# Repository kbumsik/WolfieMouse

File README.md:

# WolfieMouse

WolfieMouse is a robotics project to build [a micromouse](https://en.wikipedia.org/wiki/Micromouse). This project covers three parts:

* Robotics algorithm for maze solving (C++)
* low-level hardware driver software (C and ARM assembly)
* Tools to capture and plot robot's sensor data (Python)
* Embedded hardware design and PCB design (KiCad, an open-source alternative to Altium)

This robot won:
  * **The Special Mention Award in 2018 IEEE Region 1 Micromouse Robotics Competition**.
  * **The 3rd Place Award in 2019 IEEE Region 1 Micromouse Robotics Competition**.

## Get started

If you don't know what is micromouse competition, [this document will help.](doc/What-is-Micromouse.md).

Requires tools:
* [GNU Arm Embedded Toolchain](https://developer.arm.com/open-source/gnu-toolchain/gnu-rm) and [Makefile](https://www.gnu.org/software/make/manual/make.html) to build program for the robot.
* [OpenOCD](http://openocd.org/) to upload the program to the robot and to debug.
* [KiCad](http://kicad.org/) to design a PCB hardware.

Otherwise, a [Vagrant](https://www.vagrantup.com/) virtual machine environment is provided to skip installing the above tools.

If you whish to start with this project, see [get stared document](doc/Get-started.md).

## Documentation

See [documentation section.](doc/)

## Directory descriptions

* `doc`: Documentation folder
* `firmware`: The robot's program folder, including robotics algorithms and hardware drivers
* `simulation`: Programs to test algorithms on a desktop computer
* `tools`: Contains robot sensor data capturing tools and scripts for Vagrant machine.

## Gallery

Terminal-based simulation program. `M` stands for the position of the robot, `D` stands for the position of the goal in the maze, and `S` stands for the starting position.

Schematic overview.

PCB Footprint overview.

## License and Credits

Source code in `firmware` and `simulation` folders are licensed under [GPLv2.1](https://www.gnu.org/licenses/old-licenses/lgpl-2.1.en.html).

External libraries (FreeRTOS, CMSIS, STM32F4 HAL) under `firmware/lib` follow their own terms.

The fundamental hardware design is inspired by [Project Futura](http://micromouseusa.com/?page_id=1342) by [Green Ye](http://www.greenye.net/).

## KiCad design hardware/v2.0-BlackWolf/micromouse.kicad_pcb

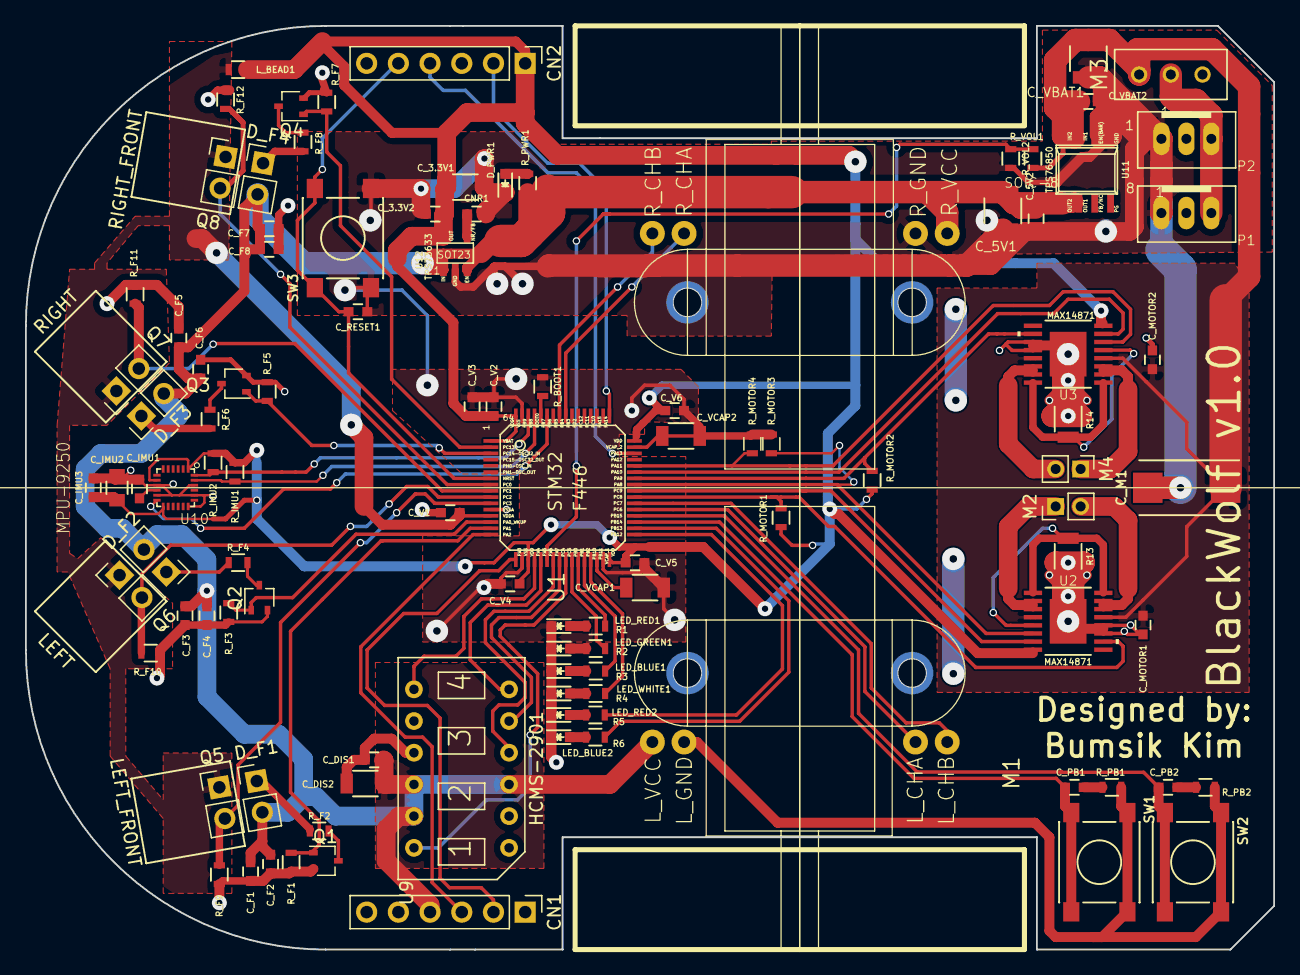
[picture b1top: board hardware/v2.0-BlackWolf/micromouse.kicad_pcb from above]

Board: 2 copper layers, 100.0 x 74.0 mm, 108 parts (0 on the bottom side), 73 nets.

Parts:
CN1, CN2: 6_PIN_HEADER; Pin_Header_Straight_1x06_Pitch2.54mm
CNR1: 0.1uF; C_0603
C_3.3V1: 10uF; C_1206
C_3.3V2, C_5V2: 0.1uF; C_0603
C_5V1: 100uF; C_1210
C_DIS1: 0.1uF; C_0603
C_DIS2: 10uF; C_1206
C_F1, C_F3, C_F5, C_F7: 4.7u; C_0603
C_F2, C_F4, C_F6, C_F8: 0.1u; C_0603
C_IMU1, C_IMU3: 0.1uF; C_0603
C_IMU2: 10nF; C_0805
C_M1: 220uF; TantalC_SizeD_EIA-7343_Reflow
C_MOTOR1, C_MOTOR2: 1uF; C_0603
C_PB1, C_PB2: 0.1uF; C_0603
C_RESET1: 0.1uF; C_0603
C_V1, C_V2, C_V3, C_V4, C_V5, C_V6: 0.1uF; C_0603
C_VBAT1: 100uF; C_1210
C_VBAT2: 0.1uF; C_0603
C_VCAP1: 4.7uF; C_1206
C_VCAP2: 2.2uF; C_1206
D_F1, D_F2, D_F3, D_F4: SFH 4545; Pin_Header_Straight_1x02_Pitch2.54mm
D_PWR1: Led_Small; LED_0603
LED_BLUE1, LED_BLUE2: Led_Small; LED_0603
LED_GREEN1: Led_Small; LED_0603
LED_RED1, LED_RED2: Led_Small; LED_0603
LED_WHITE1: Led_Small; LED_0603
LEFT: RANGE_SENSOR_HOUSING
LEFT_FRONT: RANGE_SENSOR_HOUSING
L_BEAD1: 10uH; R_0603
M1: MOTOR_MOUNTS_AND_ENCODERS; FUTURA-1.0-MOTOR-MOUNT-TEMPLATE
M2: LEFT_MOTOR; Pin_Header_Straight_1x02_Pitch2.00mm
M3: 2.54MM-SLIDE-SWITCH_TS02_SWITCH
M4: RIGHT_MOTOR; Pin_Header_Straight_1x02_Pitch2.00mm
P1, P2: B3B-PH-SM4-TB; JST_B3B-PH_HEADER
Q1, Q2, Q3, Q4: DMN3150LW; SOT-323_SC-70
Q5, Q6, Q7, Q8: TEFT4300; Pin_Header_Straight_1x02_Pitch2.54mm
R1, R2, R3, R4, R5, R6: 1k; R_0603
R13, R14: 62.5m; R_1206
RIGHT: RANGE_SENSOR_HOUSING
RIGHT_FRONT: RANGE_SENSOR_HOUSING
R_BOOT1: 10k; R_0603
R_F1, R_F3, R_F5, R_F7: 47k; R_0603
R_F2, R_F8: 10; R_0603
R_F4, R_F6: 20; R_0603
R_F9, R_F10, R_F11, R_F12: 2.4k; R_0603
R_IMU1, R_IMU2: 10k; R_0603
R_MOTOR1, R_MOTOR2, R_MOTOR3, R_MOTOR4: 10k; R_0603
R_PB1, R_PB2: 1k; R_0603
R_PWR1: 1k; R_0603
R_VOL1: 20k; R_0603
R_VOL2: 10k; R_0603
SW1, SW2, SW3: SWITCH_DPST; SW_SPST_PTS645
U1: STM32F446RE_LQFP64; STM32F446_LQFP64
U2, U3: MAX14871; TSSOP-16_EP
U9: HCMS-2901; HCMS-2903
U10: MPU-9250; QFN-24%2f3MM
U11: TPS76850; TPS76850_SOIC-8
U12: TPS73633; TPS73633_SOT-23

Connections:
+3.3VADC: C_V1.1, L_BEAD1.2, Q5.1, Q6.1, Q7.1, Q8.1, U1.VDDA
+3V3: CN2.1, C_3.3V1.1, C_3.3V2.1, C_IMU2.1, C_IMU3.1, C_V2.2, C_V3.1, C_V4.2, C_V5.2, C_V6.1, L_BEAD1.1, R_IMU1.1, R_IMU2.1, R_MOTOR1.1, R_MOTOR2.1, U1.VBAT, U1.VDD_, U2.8, U3.8, U10.1, U10.8, U10.13, U12.5
+5V: CN1.4, C_5V1.1, C_5V2.1, C_DIS1.1, C_DIS2.1, C_F1.1, C_F2.1, C_F3.1, C_F4.1, C_F5.1, C_F6.1, C_F7.1, C_F8.1, D_F1.2, D_F2.2, D_F3.2, D_F4.2, M1.L_VC, M1.R_VC, R_PWR1.1, U9.SEL, U9.V_LE, U9.V_LO, U11.5, U11.6, U12.1, U12.3
+BATT: C_M1.1, C_MOTOR1.1, C_MOTOR2.1, C_VBAT1.1, C_VBAT2.1, M3.PIN3, R_VOL1.1, U2.4, U2.13, U3.4, U3.13, U11.3, U11.4
BATT_LEVEL: R_VOL1.2, R_VOL2.1, U1.PA6
DIS_MOSI: U1.PA7, U9.D_IN
DIS_RS: U1.PC4, U9.RS
DIS_SCK: U1.PA5, U9.CLK
EMITTER_FL: Q1.1, R_F1.1, U1.PA1
EMITTER_FR: Q4.1, R_F7.1, U1.PC13
EMITTER_L: Q2.1, R_F3.1, U1.PA0_
EMITTER_R: Q3.1, R_F5.1, U1.PC14
GND: CN1.6, CN2.3, CNR1.2, C_3.3V1.2, C_3.3V2.2, C_5V1.2, C_5V2.2, C_DIS1.2, C_DIS2.2, C_F1.2, C_F2.2, C_F3.2, C_F4.2, C_F5.2, C_F6.2, C_F7.2, C_F8.2, C_IMU1.2, C_IMU2.2, C_IMU3.2, C_M1.2, C_MOTOR1.2, C_MOTOR2.2, C_RESET1.2, C_V1.2, C_V2.1, C_V3.2, C_V4.1, C_V5.1, C_V6.2, C_VBAT1.2, C_VBAT2.2, C_VCAP1.1, C_VCAP2.1, C_VCAP2.2, D_PWR1.1, LED_BLUE1.1, LED_BLUE2.1, LED_GREEN1.1, LED_RED1.1, LED_RED2.1, LED_WHITE1.1, M1.L_GN, M1.R_GN, P1.1, P2.1, Q1.2, Q2.2, Q3.2, Q4.2, R13.2, R14.2, R_BOOT1.1, R_F1.2, R_F3.2, R_F5.2, R_F7.2, R_F9.2, R_F10.2, R_F11.2, R_F12.2, R_MOTOR3.2, R_MOTOR4.2, R_PB1.2, R_PB2.2, R_VOL2.2, SW1.2, SW2.2, SW3.2, U1.VCAP, U1.VSSA, U1.VSS_, U2.11, U2.12, U2.EPAD, U3.11, U3.12, U3.EPAD, U9.BLAN, U9.GND, U10.9, U10.11, U10.18, U10.20, U10.22, U11.1, U11.2, U12.2
IMU_INT: U1.PB7, U10.12
IMU_SCL: R_IMU1.2, U1.PB8, U10.23
IMU_SDA: R_IMU2.2, U1.PB9, U10.24
LED1: R1.1, U1.PB1
LED2: R2.1, U1.PB0
LED3: R3.1, U1.PB2
LED4: R4.1, U1.PB10
LED5: R5.1, U1.PB12
LED6: R6.1, U1.PB13
MOTOR_L_DIR: U1.PC9, U2.7
MOTOR_L_PWM: R_MOTOR3.1, U1.PA8, U2.6
MOTOR_R_DIR: U1.PA10, U3.7
MOTOR_R_PWM: R_MOTOR4.1, U1.PA11, U3.6
unnamed: CNR1.1, U12.4
unnamed: C_IMU1.1, U10.10
unnamed: C_PB1.1, R_PB1.1
unnamed: C_PB2.1, R_PB2.1
unnamed: C_VCAP1.2, U1.PB11
unnamed: D_F1.1, R_F2.1
unnamed: D_F2.1, R_F4.1
unnamed: D_F3.1, R_F6.1
unnamed: D_F4.1, R_F8.1
unnamed: D_PWR1.2, R_PWR1.2
unnamed: LED_BLUE1.2, R3.2
unnamed: LED_BLUE2.2, R6.2
unnamed: LED_GREEN1.2, R2.2
unnamed: LED_RED1.2, R1.2
unnamed: LED_RED2.2, R5.2
unnamed: LED_WHITE1.2, R4.2
unnamed: M2.1, U2.2, U2.3
unnamed: M2.2, U2.14, U2.15
unnamed: M3.PIN2, P1.3, P2.3
unnamed: M4.1, U3.2, U3.3
unnamed: M4.2, U3.14, U3.15
unnamed: Q1.3, R_F2.2
unnamed: Q2.3, R_F4.2
unnamed: Q3.3, R_F6.2
unnamed: Q4.3, R_F8.2
unnamed: R13.1, U2.1, U2.5, U2.16
unnamed: R14.1, U3.1, U3.5, U3.16
unnamed: R_BOOT1.2, U1.BOOT
PB1: C_PB1.2, SW1.1, U1.PB14
PB2: C_PB2.2, SW2.1, U1.PB15
RECV_FL: Q5.2, R_F9.1, U1.PC3
RECV_FR: Q8.2, R_F12.1, U1.PC0
RECV_L: Q6.2, R_F10.1, U1.PC2
RECV_R: Q7.2, R_F11.1, U1.PC1
RESET: CN2.5, C_RESET1.1, SW3.1, U1.NRST
ROT_L_CHA: M1.L_CA, U1.PC6
ROT_L_CHB: M1.L_CB, U1.PC7
ROT_R_CHA: M1.R_CA, U1.PB4
ROT_R_CHB: M1.R_CB, U1.PB5
SWCLK: CN2.2, U1.PA14
SWDIO: CN2.4, U1.PA13
USART_RX: CN1.2, U1.PA3
USART_TX: CN1.3, U1.PA2
~DIS_CE: U1.PA4, U9.CE
~DIS_RESET: U1.PC5, U9.RESE
~MOTOR_L_FAULT: R_MOTOR1.2, U1.PC8, U2.10
~MOTOR_R_FAULT: R_MOTOR2.2, U1.PA9, U3.10

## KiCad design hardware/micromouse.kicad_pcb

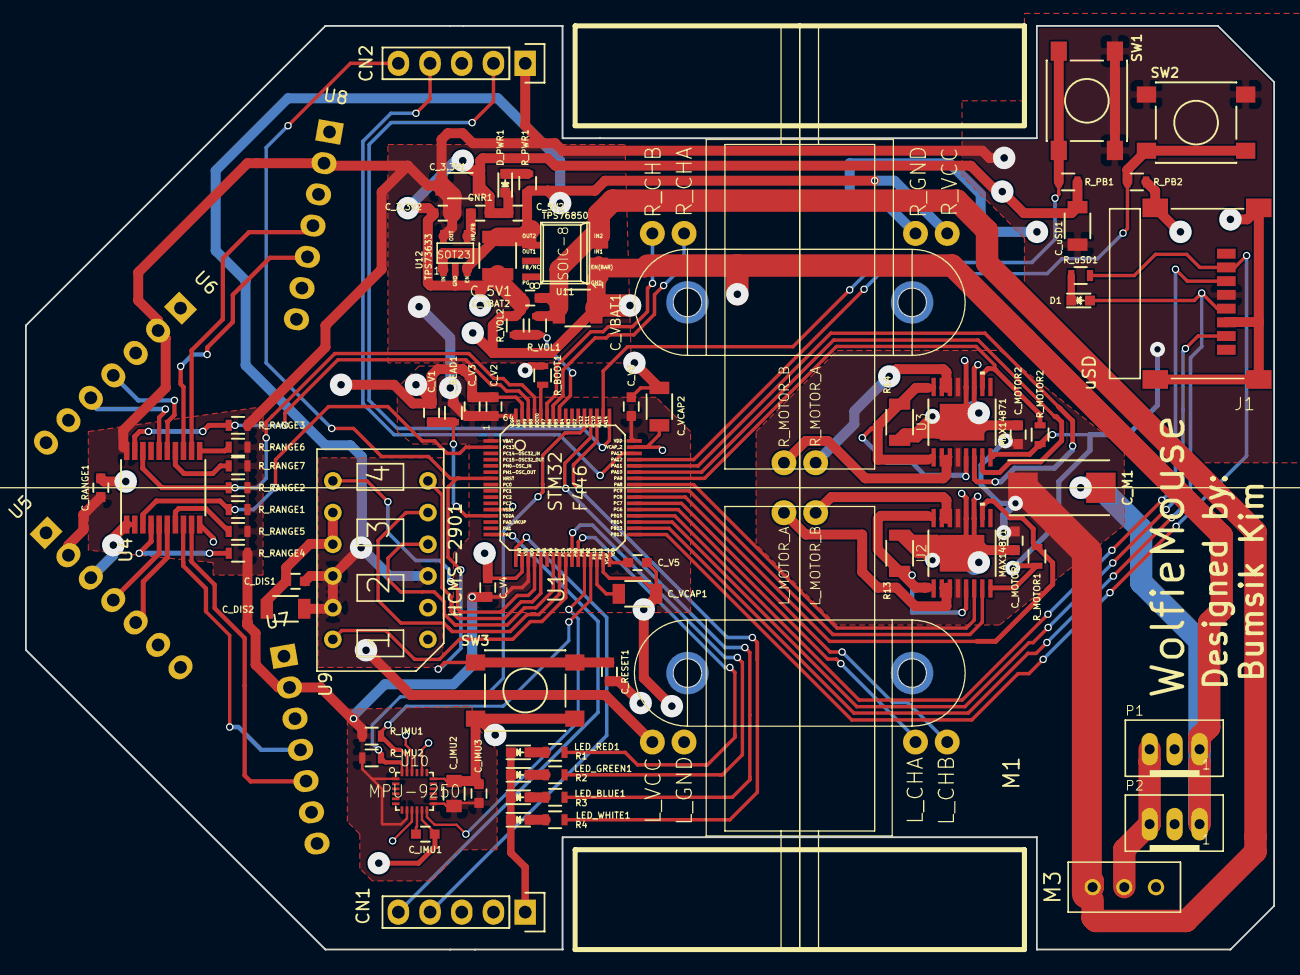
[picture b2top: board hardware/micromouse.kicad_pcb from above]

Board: 2 copper layers, 100.0 x 74.0 mm, 79 parts (0 on the bottom side), 71 nets.

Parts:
CN1, CN2: 5_PIN_HEADER; Pin_Header_Straight_1x05
CNR1: 0.1uF; C_0603
C_3.3V1: 10uF; C_1206
C_3.3V2, C_5V2: 0.1uF; C_0603
C_5V1: 100uF; C_1210
C_DIS1: 0.1uF; C_0603
C_DIS2: 10uF; C_1206
C_IMU1, C_IMU3: 0.1uF; C_0603
C_IMU2: 10nF; C_0805
C_M1: 220uF; TantalC_SizeD_EIA-7343_Reflow
C_MOTOR1, C_MOTOR2: 1uF; C_0603
C_RANGE1: 0.1uF; C_0603
C_RESET1: 0.1uF; C_0603
C_V1, C_V2, C_V3, C_V4, C_V5, C_V6: 0.1uF; C_0603
C_VBAT1: 100uF; C_1210
C_VBAT2: 0.1uF; C_0603
C_VCAP1, C_VCAP2: 2.2uF; C_1206
C_uSD1: 10uF; C_1206
D1: Led_Small; LED_0603
D_PWR1: Led_Small; LED_0603
J1: uSD_SLOT_47219-2001; uSD_MOLEX_47219-2001
LED_BLUE1: Led_Small; LED_0603
LED_GREEN1: Led_Small; LED_0603
LED_RED1: Led_Small; LED_0603
LED_WHITE1: Led_Small; LED_0603
L_BEAD1: 10uH; R_0603
M1: MOTOR_MOUNTS_AND_ENCODERS; FUTURA-1.0-MOTOR-MOUNT-TEMPLATE
M3: 2.54MM-SLIDE-SWITCH_TS02_SWITCH
P1, P2: B3B-PH-SM4-TB; JST_B3B-PH_HEADER
R1, R2, R3, R4: 1k; R_0603
R13, R14: 62.5m; R_1206
R_BOOT1: 10k; R_0603
R_IMU1, R_IMU2: 10k; R_0603
R_MOTOR1, R_MOTOR2: 10k; R_0603
R_PB1, R_PB2: 47k; R_0603
R_PWR1: 1k; R_0603
R_RANGE1, R_RANGE2, R_RANGE3, R_RANGE4, R_RANGE5, R_RANGE6, R_RANGE7: 10k; R_0603
R_VOL1: 20k; R_0603
R_VOL2: 10k; R_0603
R_uSD1: 1k; R_0603
SW1, SW2, SW3: SWITCH_DPST; SW_SPST_PTS645
U1: STM32F446RE_LQFP64; STM32F446_LQFP64
U2, U3: MAX14871; TSSOP-16_EP
U4: TCA9545A; TSSOP-20_4.4x6.5mm_Pitch0.65mm
U5, U6, U7, U8: VL6180X_POLOLU; VL6180X_POLOLU_Pin_Header_Straight_1x07
U9: HCMS-2901; HCMS-2903
U10: MPU-9250; QFN-24%2f3MM
U11: TPS76850; TPS76850_SOIC-8
U12: TPS73633; TPS73633_SOT-23

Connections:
+3.3VADC: C_V1.1, L_BEAD1.2, U1.VDDA
+3V3: CN2.1, C_3.3V1.1, C_3.3V2.1, C_IMU2.1, C_IMU3.1, C_RANGE1.1, C_V2.2, C_V3.1, C_V4.2, C_V5.2, C_V6.2, C_uSD1.1, J1.4, L_BEAD1.1, R_IMU1.1, R_IMU2.1, R_MOTOR1.1, R_MOTOR2.1, R_RANGE1.1, R_RANGE2.1, R_RANGE3.1, R_RANGE4.1, R_RANGE5.1, R_RANGE6.1, R_RANGE7.1, SW1.2, SW2.2, U1.VBAT, U1.VDD_, U2.8, U3.8, U4.20, U5.2, U6.2, U7.2, U8.2, U10.1, U10.8, U10.13, U12.5
+5V: C_5V1.1, C_5V2.1, C_DIS1.1, C_DIS2.1, M1.L_VC, M1.R_VC, R_PWR1.1, U9.SEL, U9.V_LE, U9.V_LO, U11.5, U11.6, U12.1, U12.3
+BATT: C_M1.1, C_MOTOR1.1, C_MOTOR2.1, C_VBAT1.1, C_VBAT2.1, M3.PIN3, R_VOL1.1, U2.4, U2.13, U3.4, U3.13, U11.3, U11.4
DIS_MOSI: U1.PA7, U9.D_IN
DIS_RS: U1.PC4, U9.RS
DIS_SCK: U1.PA5, U9.CLK
GND: CN1.1, CN2.3, CNR1.2, C_3.3V1.2, C_3.3V2.2, C_5V1.2, C_5V2.2, C_DIS1.2, C_DIS2.2, C_IMU1.2, C_IMU2.2, C_IMU3.2, C_M1.2, C_MOTOR1.2, C_MOTOR2.2, C_RANGE1.2, C_RESET1.2, C_V1.2, C_V2.1, C_V3.2, C_V4.1, C_V5.1, C_V6.1, C_VBAT1.2, C_VBAT2.2, C_VCAP1.2, C_VCAP2.1, C_VCAP2.2, C_uSD1.2, D_PWR1.1, J1.6, J1.G1, J1.G2, J1.G3, J1.G4, LED_BLUE1.1, LED_GREEN1.1, LED_RED1.1, LED_WHITE1.1, M1.L_GN, M1.R_GN, P1.1, P2.1, R13.2, R14.2, R_BOOT1.1, R_PB1.2, R_PB2.2, R_VOL2.2, SW3.2, U1.VCAP, U1.VSSA, U1.VSS_, U2.11, U2.12, U2.EPAD, U3.11, U3.12, U3.EPAD, U4.1, U4.2, U4.10, U5.3, U6.3, U7.3, U8.3, U9.BLAN, U9.GND, U10.9, U10.11, U10.18, U10.20, U10.22, U11.1, U11.2, U12.2
IMU_INT: U1.PB2, U10.12
IMU_SCL: R_IMU1.2, U1.PB10, U10.23
IMU_SDA: R_IMU2.2, U1.PC12, U10.24
LED1: R1.1, U1.PB1
LED2: R2.1, U1.PB0
LED3: R3.1, U1.PC11
LED4: R4.1, U1.PC10
MOTOR_L_DIR: U1.PC9, U2.7
MOTOR_L_PWM: U1.PA8, U2.6
MOTOR_R_DIR: U1.PA10, U3.7
MOTOR_R_PWM: U1.PA11, U3.6
unnamed: CNR1.1, U12.4
unnamed: C_IMU1.1, U10.10
unnamed: C_VCAP1.1, U1.PB11
unnamed: D1.1, R_uSD1.2
unnamed: D_PWR1.2, R_PWR1.2
unnamed: LED_BLUE1.2, R3.2
unnamed: LED_GREEN1.2, R2.2
unnamed: LED_RED1.2, R1.2
unnamed: LED_WHITE1.2, R4.2
unnamed: M1.L_MA, U2.2, U2.3
unnamed: M1.L_MB, U2.14, U2.15
unnamed: M1.R_MA, U3.2, U3.3
unnamed: M1.R_MB, U3.14, U3.15
unnamed: M3.PIN2, P1.3, P2.3
unnamed: R13.1, U2.1, U2.5, U2.16
unnamed: R14.1, U3.1, U3.5, U3.16
unnamed: R_BOOT1.2, U1.BOOT
unnamed: R_RANGE4.2, U4.4
unnamed: R_RANGE5.2, U4.7
unnamed: R_RANGE6.2, U4.11
unnamed: R_RANGE7.2, U4.14
unnamed: U4.5, U5.4
unnamed: U4.6, U5.5
unnamed: U4.8, U7.4
unnamed: U4.9, U7.5
unnamed: U4.12, U8.4
unnamed: U4.13, U8.5
unnamed: U4.15, U6.4
unnamed: U4.16, U6.5
PB1: R_PB1.1, SW1.1, U1.PA15
PB2: R_PB2.1, SW2.1, U1.PA12
RANGE_SCL: R_RANGE2.2, U1.PB8, U4.18
RANGE_SDA: R_RANGE3.2, U1.PB9, U4.19
RESET: CN2.5, C_RESET1.1, SW3.1, U1.NRST
ROT_L_CHA: M1.L_CA, U1.PC6
ROT_L_CHB: M1.L_CB, U1.PC7
ROT_R_CHA: M1.R_CA, U1.PB6
ROT_R_CHB: M1.R_CB, U1.PB7
SWCLK: CN2.2, U1.PA14
SWDIO: CN2.4, U1.PA13
USART_RX: CN1.4, U1.PA3
USART_TX: CN1.5, U1.PA2
VOL_METER: R_VOL1.2, R_VOL2.1, U1.PB5
uSD_MISO: J1.7, U1.PB14
uSD_MOSI: J1.3, U1.PB15
uSD_SCK: D1.2, J1.5, U1.PB13
~DIS_CE: U1.PA4, U9.CE
~DIS_RESET: U1.PC5, U9.RESE
~MOTOR_L_FAULT: R_MOTOR1.2, U1.PC8, U2.10
~MOTOR_R_FAULT: R_MOTOR2.2, U1.PA9, U3.10
~RANGE_RESET: R_RANGE1.2, U1.PC13, U4.3
~uSD_SS: J1.2, R_uSD1.1, U1.PB12

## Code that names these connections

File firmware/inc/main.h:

/**
  ******************************************************************************
  * @file           : main.h
  * @brief          : Header for main.c file.
  *                   This file contains the common defines of the application.
  ******************************************************************************
  * This notice applies to any and all portions of this file
  * that are not between comment pairs USER CODE BEGIN and
  * USER CODE END. Other portions of this file, whether 
  * inserted by the user or by software development tools
  * are owned by their respective copyright owners.
  *
  * Copyright (c) 2018 STMicroelectronics International N.V. 
  * All rights reserved.
  *
  * Redistribution and use in source and binary forms, with or without 
  * modification, are permitted, provided that the following conditions are met:
  *
  * 1. Redistribution of source code must retain the above copyright notice, 
  *    this list of conditions and the following disclaimer.
  * 2. Redistributions in binary form must reproduce the above copyright notice,
  *    this list of conditions and the following disclaimer in the documentation
  *    and/or other materials provided with the distribution.
  * 3. Neither the name of STMicroelectronics nor the names of other 
  *    contributors to this software may be used to endorse or promote products 
  *    derived from this software without specific written permission.
  * 4. This software, including modifications and/or derivative works of this 
  *    software, must execute solely and exclusively on microcontroller or
  *    microprocessor devices manufactured by or for STMicroelectronics.
  * 5. Redistribution and use of this software other than as permitted under 
  *    this license is void and will automatically terminate your rights under 
  *    this license. 
  *
  * THIS SOFTWARE IS PROVIDED BY STMICROELECTRONICS AND CONTRIBUTORS "AS IS" 
  * AND ANY EXPRESS, IMPLIED OR STATUTORY WARRANTIES, INCLUDING, BUT NOT 
  * LIMITED TO, THE IMPLIED WARRANTIES OF MERCHANTABILITY, FITNESS FOR A 
  * PARTICULAR PURPOSE AND NON-INFRINGEMENT OF THIRD PARTY INTELLECTUAL PROPERTY
  * RIGHTS ARE DISCLAIMED TO THE FULLEST EXTENT PERMITTED BY LAW. IN NO EVENT 
  * SHALL STMICROELECTRONICS OR CONTRIBUTORS BE LIABLE FOR ANY DIRECT, INDIRECT,
  * INCIDENTAL, SPECIAL, EXEMPLARY, OR CONSEQUENTIAL DAMAGES (INCLUDING, BUT NOT
  * LIMITED TO, PROCUREMENT OF SUBSTITUTE GOODS OR SERVICES; LOSS OF USE, DATA, 
  * OR PROFITS; OR BUSINESS INTERRUPTION) HOWEVER CAUSED AND ON ANY THEORY OF 
  * LIABILITY, WHETHER IN CONTRACT, STRICT LIABILITY, OR TORT (INCLUDING 
  * NEGLIGENCE OR OTHERWISE) ARISING IN ANY WAY OUT OF THE USE OF THIS SOFTWARE,
  * EVEN IF ADVISED OF THE POSSIBILITY OF SUCH DAMAGE.
  *
  ******************************************************************************
  */

/* Define to prevent recursive inclusion -------------------------------------*/
#ifndef __MAIN_H__
#define __MAIN_H__

/* Includes ------------------------------------------------------------------*/

/* USER CODE BEGIN Includes */

/* USER CODE END Includes */

/* Private define ------------------------------------------------------------*/

#define EMITTER_FR_Pin GPIO_PIN_13
#define EMITTER_FR_GPIO_Port GPIOC
#define EMITTER_R_Pin GPIO_PIN_14
#define EMITTER_R_GPIO_Port GPIOC
#define RECV_FR_Pin GPIO_PIN_0
#define RECV_FR_GPIO_Port GPIOC
#define RECV_R_Pin GPIO_PIN_1
#define RECV_R_GPIO_Port GPIOC
#define RECV_L_Pin GPIO_PIN_2
#define RECV_L_GPIO_Port GPIOC
#define RECV_FL_Pin GPIO_PIN_3
#define RECV_FL_GPIO_Port GPIOC
#define EMITTER_L_Pin GPIO_PIN_0
#define EMITTER_L_GPIO_Port GPIOA
#define EMITTER_FL_Pin GPIO_PIN_1
#define EMITTER_FL_GPIO_Port GPIOA
#define USART_TX_Pin GPIO_PIN_2
#define USART_TX_GPIO_Port GPIOA
#define USART_RX_Pin GPIO_PIN_3
#define USART_RX_GPIO_Port GPIOA
#define disPIN_CE_BAR_Pin GPIO_PIN_4
#define disPIN_CE_BAR_GPIO_Port GPIOA
#define disPIN_SCK_Pin GPIO_PIN_5
#define disPIN_SCK_GPIO_Port GPIOA
#define BATT_LEVEL_Pin GPIO_PIN_6
#define BATT_LEVEL_GPIO_Port GPIOA
#define disPIN_MOSI_Pin GPIO_PIN_7
#define disPIN_MOSI_GPIO_Port GPIOA
#define disPIN_RS_Pin GPIO_PIN_4
#define disPIN_RS_GPIO_Port GPIOC
#define disPIN_RESET_BAR_Pin GPIO_PIN_5
#define disPIN_RESET_BAR_GPIO_Port GPIOC
#define LED1_PIN_Pin GPIO_PIN_0
#define LED1_PIN_GPIO_Port GPIOB
#define LED2_PIN_Pin GPIO_PIN_1
#define LED2_PIN_GPIO_Port GPIOB
#define usdPIN_SS_BAR_Pin GPIO_PIN_12
#define usdPIN_SS_BAR_GPIO_Port GPIOB
#define usdPIN_SCK_Pin GPIO_PIN_13
#define usdPIN_SCK_GPIO_Port GPIOB
#define usdPIN_MISO_Pin GPIO_PIN_14
#define usdPIN_MISO_GPIO_Port GPIOB
#define usdPIN_MOSI_Pin GPIO_PIN_15
#define usdPIN_MOSI_GPIO_Port GPIOB
#define counterPIN_L_CHA_Pin GPIO_PIN_6
#define counterPIN_L_CHA_GPIO_Port GPIOC
#define counterPIN_L_CHB_Pin GPIO_PIN_7
#define counterPIN_L_CHB_GPIO_Port GPIOC
#define motorPIN_L_FAULT_BAR_Pin GPIO_PIN_8
#define motorPIN_L_FAULT_BAR_GPIO_Port GPIOC
#define motorPIN_L_DIR_Pin GPIO_PIN_9
#define motorPIN_L_DIR_GPIO_Port GPIOC
#define motorPIN_L_PWM_Pin GPIO_PIN_8
#define motorPIN_L_PWM_GPIO_Port GPIOA
#define motorPIN_R_FAULT_BAR_Pin GPIO_PIN_9
#define motorPIN_R_FAULT_BAR_GPIO_Port GPIOA
#define motorPIN_R_DIR_Pin GPIO_PIN_10
#define motorPIN_R_DIR_GPIO_Port GPIOA
#define motorPIN_R_PWM_Pin GPIO_PIN_11
#define motorPIN_R_PWM_GPIO_Port GPIOA
#define PB2_PIN_Pin GPIO_PIN_12
#define PB2_PIN_GPIO_Port GPIOA
#define TMS_Pin GPIO_PIN_13
#define TMS_GPIO_Port GPIOA
#define TCK_Pin GPIO_PIN_14
#define TCK_GPIO_Port GPIOA
#define PB1_PIN_Pin GPIO_PIN_15
#define PB1_PIN_GPIO_Port GPIOA
#define LED4_PIN_Pin GPIO_PIN_10
#define LED4_PIN_GPIO_Port GPIOC
#define LED3_PIN_Pin GPIO_PIN_11
#define LED3_PIN_GPIO_Port GPIOC
#define SWO_Pin GPIO_PIN_3
#define SWO_GPIO_Port GPIOB
#define counterPIN_R_CHA_Pin GPIO_PIN_4
#define counterPIN_R_CHA_GPIO_Port GPIOB
#define counterPIN_R_CHB_Pin GPIO_PIN_5
#define counterPIN_R_CHB_GPIO_Port GPIOB
#define imu_INT_Pin GPIO_PIN_7
#define imu_INT_GPIO_Port GPIOB
#define imuPIN_SCL_Pin GPIO_PIN_8
#define imuPIN_SCL_GPIO_Port GPIOB
#define imuPIN_SDA_Pin GPIO_PIN_9
#define imuPIN_SDA_GPIO_Port GPIOB

/* ########################## Assert Selection ############################## */
/**
  * @brief Uncomment the line below to expanse the "assert_param" macro in the 
  *        HAL drivers code
  */
 #define USE_FULL_ASSERT    1U 

/* USER CODE BEGIN Private defines */

/* USER CODE END Private defines */

#ifdef __cplusplus
 extern "C" {
#endif
void _Error_Handler(char *, int);

#define Error_Handler() _Error_Handler(__FILE__, __LINE__)
#ifdef __cplusplus
}
#endif

#endif /* __MAIN_H__ */

/************************ (C) COPYRIGHT STMicroelectronics *****END OF FILE****/

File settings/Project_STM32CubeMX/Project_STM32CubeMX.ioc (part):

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Mcu.Name=STM32F446R(C-E)Tx
Mcu.Package=LQFP64
Mcu.UserName=STM32F446RETx
PA10.GPIOParameters=GPIO_Label
PA10.GPIO_Label=motorPIN_R_DIR
PA10.Signal=GPIO_Output
PA11.GPIOParameters=GPIO_Label
PA11.GPIO_Label=motorPIN_R_PWM
PA11.Signal=S_TIM1_CH4
PA12.GPIOParameters=GPIO_Label
PA12.GPIO_Label=PB2_PIN
PA12.Signal=GPXTI12
PA13.GPIOParameters=GPIO_Label
PA13.GPIO_Label=TMS
PA13.Mode=Trace-Asynchronous_SW
PA13.Signal=SYS_JTMS-SWDIO
PA14.GPIOParameters=GPIO_Label
PA14.GPIO_Label=TCK
PA14.Mode=Trace-Asynchronous_SW
PA14.Signal=SYS_JTCK-SWCLK
PA15.GPIOParameters=GPIO_Label
PA15.GPIO_Label=PB1_PIN
PA15.Signal=GPXTI15
PA2.GPIOParameters=GPIO_Label
PA2.GPIO_Label=USART_TX
PA2.Mode=Asynchronous
PA2.Signal=USART2_TX
PA3.GPIOParameters=GPIO_Label
PA3.GPIO_Label=USART_RX
PA3.Mode=Asynchronous
PA3.Signal=USART2_RX
PA4.GPIOParameters=GPIO_Label
PA4.GPIO_Label=disPIN_CE_BAR
PA4.Signal=GPIO_Output
PA5.GPIOParameters=GPIO_Label
PA5.GPIO_Label=disPIN_SCK
PA5.Mode=Full_Duplex_Master
PA5.Signal=SPI1_SCK
PA6.GPIOParameters=GPIO_Label
PA6.GPIO_Label=disPIN_MISO
PA6.Mode=Full_Duplex_Master
PA6.Signal=SPI1_MISO
PA7.GPIOParameters=GPIO_Label
PA7.GPIO_Label=disPIN_MOSI
PA7.Mode=Full_Duplex_Master
PA7.Signal=SPI1_MOSI
PA8.GPIOParameters=GPIO_Label
PA8.GPIO_Label=motorPIN_L_PWM
PA8.Signal=S_TIM1_CH1
PA9.GPIOParameters=GPIO_Label
PA9.GPIO_Label=motorPIN_R_FAULT_BAR
PA9.Signal=S_TIM1_CH2
PB0.GPIOParameters=GPIO_Label
PB0.GPIO_Label=LED1_PIN
PB0.Signal=GPIO_Output
PB1.GPIOParameters=GPIO_Label
PB1.GPIO_Label=LED2_PIN
PB1.Signal=GPIO_Output
PB10.GPIOParameters=GPIO_Label
PB10.GPIO_Label=imuPIN_SCL
PB10.Mode=I2C
PB10.Signal=I2C2_SCL
PB12.GPIOParameters=GPIO_Label
PB12.GPIO_Label=usdPIN_SS_BAR
PB12.Signal=SPI2_NSS
PB13.GPIOParameters=GPIO_Label
PB13.GPIO_Label=usdPIN_SCK
PB13.Mode=Full_Duplex_Master
PB13.Signal=SPI2_SCK
PB14.GPIOParameters=GPIO_Label
PB14.GPIO_Label=usdPIN_MISO
PB14.Mode=Full_Duplex_Master
PB14.Signal=SPI2_MISO
PB15.GPIOParameters=GPIO_Label
PB15.GPIO_Label=usdPIN_MOSI
PB15.Mode=Full_Duplex_Master
PB15.Signal=SPI2_MOSI
PB2.GPIOParameters=GPIO_Label
PB2.GPIO_Label=imuPIN_INT
PB2.Signal=GPXTI2
PB3.GPIOParameters=GPIO_Label
PB3.GPIO_Label=SWO
PB3.Mode=Trace-Asynchronous_SW
PB3.Signal=SYS_JTDO-SWO
PB5.GPIOParameters=GPIO_Label
PB5.GPIO_Label=VOL_METER_PIN
PB5.Signal=GPIO_Analog
PB6.GPIOParameters=GPIO_Label
PB6.GPIO_Label=rotPIN_L_CHA
PB6.Signal=S_TIM4_CH1
PB7.GPIOParameters=GPIO_Label
PB7.GPIO_Label=rotPIN_L_CHB
PB7.Signal=S_TIM4_CH2
PB8.GPIOParameters=GPIO_Label
PB8.GPIO_Label=rangePIN_SCL
PB8.Mode=I2C
PB8.Signal=I2C1_SCL
PB9.GPIOParameters=GPIO_Label
PB9.GPIO_Label=rangePIN_SDA
PB9.Mode=I2C
PB9.Signal=I2C1_SDA
PC10.GPIOParameters=GPIO_Label
PC10.GPIO_Label=LED4_PIN
PC10.Signal=GPIO_Output
PC11.GPIOParameters=GPIO_Label
PC11.GPIO_Label=LED3_PIN
PC11.Signal=GPIO_Output
PC12.GPIOParameters=GPIO_Label
PC12.GPIO_Label=imuPIN_SDA
PC12.Mode=I2C
PC12.Signal=I2C2_SDA
PC13.GPIOParameters=GPIO_Label,GPIO_ModeDefaultEXTI
PC13.GPIO_Label=rangePIN_RESET_BAR
PC13.GPIO_ModeDefaultEXTI=GPIO_MODE_EVT_RISING
PC13.Signal=GPXTI13
PC14-OSC32_IN.Signal=RCC_OSC32_IN
PC15-OSC32_OUT.Signal=RCC_OSC32_OUT
PC4.GPIOParameters=GPIO_Label
PC4.GPIO_Label=disPIN_RS
PC4.Signal=GPIO_Output
PC5.GPIOParameters=GPIO_Label
PC5.GPIO_Label=disPIN_RESET_BAR
PC5.Signal=GPIO_Output
PC6.GPIOParameters=GPIO_Label
PC6.GPIO_Label=rotPIN_R_CHA
PC6.Signal=S_TIM3_CH1
PC7.GPIOParameters=GPIO_Label
PC7.GPIO_Label=rotPIN_R_CHB
PC7.Signal=S_TIM3_CH2
PC8.GPIOParameters=GPIO_Label
PC8.GPIO_Label=motorPIN_L_FAULT_BAR
PC8.Signal=GPXTI8
PC9.GPIOParameters=GPIO_Label
PC9.GPIO_Label=motorPIN_L_DIR
PC9.Signal=GPIO_Output
PH0-OSC_IN.Signal=RCC_OSC_IN
PH1-OSC_OUT.Signal=RCC_OSC_OUT
RCC.HSE_VALUE=8000000
RCC.SYSCLKFreq_VALUE=90000000
RCC.SYSCLKSource=RCC_SYSCLKSOURCE_PLLCLK
board=NUCLEO-F446RE
boardIOC=true

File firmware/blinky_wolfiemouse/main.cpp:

#include "trace.h"
#include "tick.h"
// KB library
#include "system_config.h"
#include "gpio.h"
#include "terminal.h"
#include "hcms_290x_display.h"

// FreeRTOS
#include "FreeRTOS.h"
#include "portable.h" // TODO: Delete
#include "task.h"
#include "timers.h"
#include "queue.h"
#include "semphr.h"
#include "event_groups.h"

void on_pressed(void);

static void task_blinky(void *pvParameters);

/* Task Handlers */
TaskHandle_t task_blinky_handler;


int main(void)
{
    // initialize clock and system configuration
    system_init();

    // Initialize all configured peripherals
    peripheral_init();

    /* Initial LED Display message */
    hcms_290x_matrix("BOOT");

    // Set interrupt button
    gpio_init_t GPIO_InitStruct;
    GPIO_InitStruct.Mode = GPIO_MODE_INPUT;
    GPIO_InitStruct.Pull = NOPULL;
    gpio_isr_enable(B1_PORT, B1_PIN, &GPIO_InitStruct, RISING_EDGE);
    gpio_isr_register(B1_PORT, B1_PIN, on_pressed);


    // Toggle LED once
    gpio_toggle(LED1_PORT, LED1_PIN);
    gpio_toggle(LED2_PORT, LED2_PIN);
    gpio_toggle(LED3_PORT, LED3_PIN);
    gpio_toggle(LED4_PORT, LED4_PIN);
    gpio_toggle(LED5_PORT, LED5_PIN);
    gpio_toggle(LED6_PORT, LED6_PIN);

    // wait for .5 second
    delay_ms(500);
    gpio_toggle(LED1_PORT, LED1_PIN);
    gpio_toggle(LED2_PORT, LED2_PIN);
    gpio_toggle(LED3_PORT, LED3_PIN);
    gpio_toggle(LED4_PORT, LED4_PIN);
    gpio_toggle(LED5_PORT, LED5_PIN);
    gpio_toggle(LED6_PORT, LED6_PIN);

    trace_puts("Hello ARM World!");
    terminal_puts("Hello World!\n");

    BaseType_t result;
    /* definition and creation of defaultTask */
    result = xTaskCreate(
            task_blinky,            /* Pointer to the function that implements the task */
            "Blinky",               /* Text name for the task. This is to facilitate debugging only. It is not used in the scheduler */
            configMINIMAL_STACK_SIZE, /* Stack depth in words */
            NULL,                   /* Pointer to a task parameters */
            1,                      /* The task priority */
            &task_blinky_handler);  /* Pointer of its task handler, if you don't want to use, you can leave it NULL */

    if (result != pdPASS) {
        KB_DEBUG_ERROR("Creating task failed!!");
    }
    /* Do not put delay function in this section!
     * Because xTaskCreate will stop systick until the scheduler called */
    // TODO: check if it is true
    /* Start scheduler */
    vTaskStartScheduler();
    while (1) {
    }
}

void on_pressed(void)
{
    trace_puts("Button Pressed\n");
    return;
}

/* vBlinkyTask function */
void task_blinky(void *pvParameters)
{
    portTickType xLastWakeTime;
    /* Initialize xLastWakeTime for vTaskDelayUntil */
    /* This variable is updated every vTaskDelayUntil is called */
    xLastWakeTime = xTaskGetTickCount();

    uint32_t seconds = 0;

    while (1) {
        gpio_toggle(LED1_PORT, LED1_PIN);
        gpio_toggle(LED2_PORT, LED2_PIN);
        gpio_toggle(LED3_PORT, LED3_PIN);
        gpio_toggle(LED4_PORT, LED4_PIN);
        gpio_toggle(LED5_PORT, LED5_PIN);
        gpio_toggle(LED6_PORT, LED6_PIN);
        ++seconds;
        // Count seconds on the trace device.
        trace_printf("Second %u\n", seconds);

        /* Call this Task explicitly every 50ms ,NOT Delay for 50ms */
        vTaskDelayUntil(&xLastWakeTime, (500 / portTICK_RATE_MS));
    }

    /* It never goes here, but the task should be deleted when it reached here */
    vTaskDelete(NULL);
}

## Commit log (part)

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2016-01-18 updated basic CubeMX project
2016-01-19 updated working test project
2016-02-02 Added simulation and algorithm part - 80% completed.
2016-02-08 updated MouseController.cpp
2016-02-09 reverted the changes back
    --eric
2016-02-29 added example_main.cpp
2016-03-31 updated PCB design
2016-03-31 PCB updated
2016-04-04 Finished the PCB
2016-04-04 Fixed for the PCB manufacturer requirements
2016-04-05 Uploaded bill of materials
2016-04-06 The range finder is all working. Integrating MUX needed
2016-04-06 Changed the PCB design to meet the manufacturer's requirement
2016-04-08 Compilation good
2016-04-08 Applied Formatter
2016-04-09 Printing and Saving simulation Good
2016-04-10 Floodfill algorithm good
2016-04-11 1. C++ object initialization problem fixed 2. Queue is working well. 3. But path algorithm needs work. it does not reach to the goal
2016-04-15 1. added the main project 2. changed the freq of the MCU, just for a while
2016-04-15 all four Range finders working well
2016-04-15 added LED pins
2016-04-15 saved-encoder and motor
2016-04-16 Motor driver OK
2016-04-16 1.Rotary encoder works well 2.The measurements is added
2016-04-16 updated test project
2017-01-05 2017 Micromouse initial setup start
2017-01-06 added vagrantfile
2017-01-08 Added Makefile
2017-01-10 wrote a Dockerfile (incomplete)
2017-01-14 provisioning for GNU ARM Eclipse
2017-01-14 Added RDP/VNC server. All Vagrant/VirtualBox configurations are set.
2017-01-15 Fixed Eclipse mars hanging problem with GTK3
2017-01-15 Changed macro name and position
2017-01-16 Applied Linux style coding convention. Separate Enum and Struct to their own file.
2017-01-16 Modified README.md
2017-01-16 Fixed some markdown typo
2017-01-16 Fixed enum convention for C++
2017-01-18 Only moved order of definitions to improve readability
2017-01-18 Deleted init() functions in each class, using C++11 style delegating constructor.
2017-01-21 Add Gitter badge
2017-01-24 added .gitattributes
2017-01-24 updateCell() replaced with printMaze() in MouseController class. printMaze() overrides printMaze method in the MazeIO class
2017-01-24 printMaze in Maze class was made virtual
2017-01-24 change the name of class design directory
2017-01-24 added class design documentation
2017-01-24 Resolved some compiler warnings (initialization list order and compound literal)
2017-02-05 Merged finder and interface implementation classes
2017-02-05 Added hardware designs
2017-02-06 changed structure of documentation
2017-02-07 Fixed broken image
2017-02-07 changed PNG file with JPG
2017-02-07 Add them again
2017-02-07 Try deleting again after fixing .gitattributes
2017-02-08 A draft of report.
2017-02-08 added What-is-micromouse
2017-02-14 chagned Vagrant script
2017-02-14 added more instructions
2017-02-15 fixed Makefile
2017-02-16 Deleted unnesecessary script folder
2017-02-16 Added kb-lib
2017-02-16 Fixed Vagrant file
2017-02-16 updated kb-lib for Makefile
2017-02-16 attendace file added
2017-02-16 I changed ATENDEE.ed
2017-02-17 Completed writing GIthub-HOWTO
2017-02-17 Added hardware design document
2017-02-22 Added design goal for v2.0 and 3D models
2017-03-05 FIxed the invalid cell problem. New function was added to the Maze.hpp.
2017-03-05 Added empty Finder and Mover Interfaces
2017-03-10 Changed Pop/push order and a decision on adjacent cell
2017-03-10 Maze.hpp: Added methods for Position struct
2017-03-10 Applied to MouseController.cpp
2017-03-11 Made it so that the mouse points in the direction it is going
2017-03-11 Coding conventions kept and code simplified
2017-03-16 added experimental PyTTY.
2017-03-17 4 goals are supported now in algorith and maze class.
2017-03-17 destinations member in MouseController class was configured. The algorithm uses destinations now and boolean methods were added. Maybe we can add another method to add destinations.
2017-03-18 Hardware driver cleanup
2017-03-19 Default goals only added when no file is loaded. Otherwise goals from file are used
2017-03-19 Destinations fully implemented. The mouse will set the goals as destinations at initialization. The algorithm will find destinations one by one and the mouse will move to each one until reaching the 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
2017-03-19 Enabled FreeRTOS and onButtonPressed event for blinky project
2017-03-21 Improved encoder update scheme
2017-03-21 Change name of peripherals.c
2017-03-22 Added a new pcb board folder
2017-03-29 added BlackWolf hardware project - on progress!
2017-03-30 BlackWolf PCB design completed
2017-03-30 PCB into production. Directory cleanup
2017-03-30 Mouse will go to goal then it will explore 4 unsearched cells then it will go home. It will repeat this.
2017-03-30 small fix
2017-04-02 Improved encoder update scheme
    Change name of peripherals.c
    Added simple pid control
2017-04-02 minor fix on initializing.
2017-04-04 FSM was implamented. The mouse is in three states. goGoal, explore, goStart.
2017-04-05 Divided project directory into boards
2017-04-05 added a simple sensor test in Nucleo-blinky
2017-04-06 Algorithm runs only when it new data of a cell is found
2017-04-07 Speed-based PID PWM control updated
2017-04-07 Added range sensr-based rotational PID control
2017-04-07 Provide system function for convenient control
2017-04-07 added skeleton main FSM
2017-04-07 Added going straight test to the FSM
2017-04-08 updated kb_lib
2017-04-08 This is the last code for the competition
2017-04-20 deleted unnessccary bsp
2017-04-20 Changed object model of motor and encoder
2017-04-22 Implemented turning operation for motion control
2018-03-07 PCB: Fixed wrong NMOS pinmap
2018-03-07 PCB: Fixed floating PWM output problem
2018-03-08 PCB: Separated 5V source due to heat
2018-03-08 PCB: Added Via Stitching
2018-03-15 CAM created
2018-03-15 Added VS code workspace
2018-03-15 Added latest STM32F4 HAL from kb_lib
2018-03-15 Added latest FreeRTOS from kb_lib
2018-03-15 Hardware: Updated STM32CubeMX project to remove fatfs
2018-03-15 Changed kb_lib path
2018-03-15 Changed kb_lib submodule to plain directory
2018-03-16 Deleted kb_lib, moving components to firmware folder
2018-03-16 Reordered projects folder, moving firmware sources
2018-03-16 FIrmware: FIrst Makefile blinky project (NOT PERFECT YET)
2018-03-16 Makefile: Now it covers all components
2018-03-16 System_stm32f4xx.c updated to the latest
2018-03-16 Blinkey: First successful flashing to WolfieMouse board using Makefile
2018-03-16 Deleted outdated main_project
2018-03-17 Env: Updated Vagrant environment. Cleanup some settings files
2018-03-17 Added the project's root Makefile
2018-03-18 modified comment for the test
2018-03-18 Revert 29ab2d , Created Makefile porject for Simuation.
2018-03-18 Simul: Reverted out.txt
2018-03-18 Changed cpp file to cc
2018-03-18 Simul: check if files exists
2018-03-19 Tool: fixed /usr/local/sbin:/usr/local/bin:/usr/bin:/usr/lib/emscripten:/usr/lib/jvm/default/bin:/usr/bin/site_perl:/usr/bin/vendor_perl:/usr/bin/core_perl:/home/kbumsik/opt/emsdk-portable:/home/kbum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
2018-03-19 Blinky: Added Measuring rotary encoder
2018-03-20 Encoder: changed to struct based
2018-03-20 Range: separated .c file for range sensor
2018-03-21 edit pathfinder using char
2018-03-21 using enum and modified algorithms
2018-03-22 Simul: Changed enum characters for readiability
2018-03-22 left, right turn case during moving horizontal algorithm fix
2018-03-22 PID: set parameters for mouse. Working well
2018-03-22 adjust algorithm about locationg mouse to the center
2018-03-22 remove vscode setting.json
2018-03-23 removed out.txt file
2018-03-23 Forgot to switch the functions in main
2018-03-23 Mouse: Added Thread based motor control, not interrupt
2018-03-23 Modified the linker as to reserve sector 1. sector 0 cannot be used. Test program created and verified proper reading
2018-03-23 IMPORTANT: Best PID for forward moving, PWM frequency, baud rate changes
2018-03-23 direction coordinate modified(memory -> Decart)
2018-03-23 re upload after coordinate swap
2018-03-24 Cmd: Added smooth turn (not perfect) and "back start to center" commands
2018-03-24 segmentaition fault(core dumped) fix
2018-03-24 PID: added header file
2018-03-24 FlashIO class added. this will make it possible for our mouse to save and read data from flash
2018-03-24 Tools: Added Jlink OB, and stdc++ lib
2018-03-24 Created competition mouse, fixed RealMouse
2018-03-24 Polling control of mouse
2018-03-24 Quick fix
2018-03-27 Fixed SimulMouse
2018-03-28 Firmware: source cleanup
2018-03-28 .vscode: Deleted Windows and Mac settings
2018-03-28 Doc: updated Readme.md
2018-03-31 Makefile: Added Windows Subsystem for Linux (WSL) support
2018-04-01 simulation: Deleted out.txt
2018-04-01 Makefile: cleanup
2018-04-02 VS Code: Added full support for debugging in VS Code
2018-04-08 IOInterface: Added IOInterface::read()
2018-04-08 Simul: added string-contructed maze example
2018-04-08 Blinky_wolfimouse: Now it can run simulation
2018-04-08 MazeIO: now it correctly detects if maze data exists
2018-04-08 flash: Fixed first earsing failed problem
2018-04-08 FlashIO: Added to blinky_nucleo
2018-04-09 MouseController: Fixed bug on moving, Introduced scanAndMove() to reduce redundant codes
2018-04-09 MouseController: reorder methods
2018-04-09 Maze: fixed some compiler warnings
2018-04-09 MouseController: Fixed the mouse hangs when all destination reached
2018-04-09 Fixed some compiler warnings
2018-04-10 Firmware: Deleted system_control.h
2018-04-10 CMD: Added range sensor reading (UNTESTED)
2018-04-11 PathFinder: now it prints the three cases
2018-04-11 Pathfinder: duplication counting
2018-04-12 Added clang-format
2018-12-21 Create To do
2019-03-01 Updated for 2019
2019-03-01 Add leading project_ for project folders
2019-03-01 Add YouTube videos for installing software.
2019-03-02 Rename: blinky_nucleo64 => simulation_nucleo64
2019-03-02 Re-organize FSM table
2019-03-03 Main: Change FreeRTOS task name => thread to avoid name confilct with FSM tasks
2019-03-03 Main: change the naming conventions
2019-03-03 VSCode-CppTools: Deleted hard-coded includePath
2019-03-03 Main: merge with maze_solver
2019-03-03 Main: Separated button handling functions
2019-03-04 Main: Show task numbers on LED
2019-03-04 Terminal: Add more baud rate options
2019-03-04 VSCode: Updated include path for windows
2019-03-05 Control_loop: Use inline functions instead of FreeRTOS macros for readability
2019-03-05 Main: Implement basic tasks
2019-03-05 Main: Add descriptions of each tasks
2019-03-05 Control_loop: change the order of cmd_type enum
2019-03-06 Logger: First logger implementation
2019-03-06 src: moved some headers in board to module (without modification)
2019-03-06 project_blinky_wolfiemouse: Deleted
2019-03-06 Revert "Project reorganization: Moved project-specific codes to the common src folder"
2019-03-06 Fix logger
2019-03-06 Logger: Add logger test to simulation_nucleo64
2019-03-06 Log: updated plot.py to visualize
2019-03-07 Fix incorrect priority settings #73
2019-03-07 FSM: Fix issue with running next state's task instead of the current state.
2019-03-08 Turn off logger for performance reason
2019-03-08 Tools: Plot data over time
2019-03-08 FreeRTOS: use configUSE_PORT_OPTIMISED_TASK_SELECTION
2019-03-08 Rename: control_loop_thread_wait_until_1ms() => control_loop_thread_wait_1ms()
2019-03-08 Add CMD_MOVE_UNTIL_FRONT_WALL
2019-03-09 Plot.py: Last update
2019-03-09 update PID
2019-03-09 config_measurements.h: Move header to control_loop_thread_dirver.c
2019-03-09 Control_loop call xQueueSend inside of control_loop instead of cmd.d
2019-03-09 Add CMD_SENSOR_GET_RANGE and delete global range data
2019-03-09 cmd: change name CMD_LOW_* => CMD_NONBLOCK_*
2019-03-09 Control_loop: reduced size of queue
2019-03-09 MouseController: Add Optimizer, but not using it yet
2019-03-09 Added Move_until_wall
2019-03-09 Turn off side ranges when closing to the front wall
2019-03-09 Range: change name: front -> front_left
2019-03-10 Control_loop_thread: move peripheral initilization code to system_config.c
2019-03-10 Control_loop_thread.c: Moved to src/module
2019-07-04 Add fish shell for Vagrant, add Alacritty config
2019-07-07 Vagrant: Add USB serial kernel modules
2019-08-06 Vagrant: switch to zsh environment, add CoolTerm
2019-08-08 Vagrant: Add common config.sh, move bashrc=>zshrc
2019-08-08 Simulation: Add control loop
